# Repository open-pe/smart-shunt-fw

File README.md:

A versatile isolated power monitor based on INA228.
I made this for precision power metering and testing DCDC converters.

* Digital Signal isolators for i2c and alert
* Isolated power supply
* battery connector
* optional Vbus voltage divider for dc bus voltages above 85V
* programmable i2c address
* NTC for shunt temperature measurement (in addition to the INA228 internal temperature sensor)

# Building

## Platformio Setup

* [install script](https://docs.platformio.org/en/latest/core/installation/methods/installer-script.html)
* [setup shell commands](https://docs.platformio.org/en/latest/core/installation/shell-commands.html)
* [clion](https://docs.platformio.org/en/latest/integration/ide/clion.html)

select the board:

`pio run -e esp32s3`
or
`pio run -e stm32h5`

# TODO

- add ssa-100 plug?
- add ntc
- add pin header for chassis mount resistor
- jumper to disconnect on-board shunt?
- add RSN-50-50 footprint (no available)
- add external alert (for OC shutdown)
- add external IO pins?

Supported ADC:

* ADS1115 / ADS 1015 (for example with SSA-100)
* INA226 (16-bit)
* INA228 (20-bit, 85V)
* ADS1262 (32-bit)
* ADS131M0x (24-bit sim. sampling)
* TODO ADS127L11

On startup it detects the ADCs on the I2C bus using there default addresses.

I tested it on these MCUs:

* ESP8266
* ESP32
* ESP32-S3

The program reads voltage and current and computes power.
It integrates power for energy measurement using the trapezoidal rule.

# Output

* Serial (human friendly logs)
* UDP messages using InfluxDB line protocol

# Voltage Divider Resistors

Resistors with low temperature drift are favourable. Tolerance is not so important because we can simply calibrate.
Consider the ADC input impedance when designing the voltage divider.
Thin film or metal film resistors. Cheap ($.5) SMD chip resistors with 10ppm/°C.
Resistors with 5ppm/°C drift cost $2.
Choose resistors with equal drift, so drift get eliminated.

# Current Sense Resistors

https://www.researchgate.net/profile/Gunnar-Fernqvist/publication/224304168_Characteristics_of_burden_resistors_for_high-precision_DC_current_transducers/links/65ad0815f323f74ff1e064ab/Characteristics-of-burden-resistors-for-high-precision-DC-current-transducers.pdf
https://accelconf.web.cern.ch/p07/papers/MOPAN071.pdf
"The highest precision is offered by a proprietary Zeranin wire design from Hitec,"
=> Bulk Metal Foil or “foil”.

https://accelconf.web.cern.ch/p77/PDF/PAC1977_1810.PDF

10A <1ppm reference https://cds.cern.ch/record/643293/files/cer-002399330.pdf

https://www.datatec.eu/caenels-ct-100-c
https://www.datatec.eu/stromwandler-dcct
https://www.datatec.eu/caenels-ct-100v-p

A CT100-P with Y007810R0000B9L (10ohm, 0ppm/K) or 4-terminal Y169025R0000T9L (25ohm, 0.2ppm/K)
with 25ohms: 25mV/A (equiv burden 25mΩ, and almost no self-heat)

Low drift is important. Drift can be compensated with temperature measurement.
Consider max current and power dissipation. For resistances <=1mΩ it is hard to find low drift SMD chip resistors.
A chassis mount resistor might be a better choice for current measurement >40 A.

Riedon https://riedon.com/resistors/current-sense/
VPG

RUG-Z isabellenhuette

# Current Reference

https://doc.xdevs.com/doc/_Metrology/wang2014.pdf

# Resistor References

Tinsley 1682 https://www.ebay.com.au/itm/385633870779
J.L. William Scientific Instruments 0.1 Ohm Cal Standard DC Resistor (SN: 3127) (10 amp)
3928 (14amp)

## SMD Resistors

| MFR            | MPN                     | mΩ  | P   | Imax | tol | TCR           | padW/mm | padH/mm | 4wire | px100 |                                                                                       |
|----------------|-------------------------|-----|-----|------|-----|---------------|---------|---------|-------|-------|---------------------------------------------------------------------------------------|
| isabellenhütte | BVR-Z-R0003-1.0         | .3  | 11W |      | 1%  | 20ppm         | 5.5     | 1.6     | y     | $1.9  |                                                                                       |
| bourns         | CSS2H-2512R-L300F       | .3  | 6W  |      |     | 150ppm(50ppm) | 3.4     | 1.8     | n     | $     |                                                                                       |
| Milliohm (CN)  | HoLRS5930-0.3mR-1%      | .3  | 7W  |      | 1%  | 50ppm         | 7.6     | 4.2     | n     | $.24  |                                                                                       |
| vishay         | WSLP5931L3000FEA        | .3  | 10W |      | 1%  | 175ppm        | 7.75    | 5.2     | n     | $1.7  |                                                                                       |
| RESI (CN)      | SEWF3951DL300P9         | .3  | 15W |      | .5% | 25ppm         | 13      | 2       | n     | $2.2  |                                                                                       |
| isabellenhütte | BVR-Z-R0005-1.0         | .5  |     |      | 1%  | 20ppm         |         |         |       |       |                                                                                       |
|                | BVR-M-R0007-1.0         | .7  | 8W  |      | 1%  | 20ppm         |         |         |       |       |                                                                                       |
|                | BVR-M-R001              | 1   | 7W  |      |     | 50ppm         |         |         |       |       |                                                                                       |
| vishay         | Y14880R00100D0R         | 1   | 3W  |      | .5% | 15ppm         |         |         | y     |       |                                                                                       |
|                | WSK12161L000FEA/B       | 1   | 3W  |      | .1% | 20ppm         |         |         |       |       |                                                                                       |
|                | Y14880R00200B9R         | 2   | 3W  |      | .1% | 15ppm         |         |         | y     |       |                                                                                       |
|                | Y14730R00300B0R         | 3   | 3W  | 31A  | .1% | 5ppm          |         |         |       |       |                                                                                       |
|                | Y14750R10000B9R         | 100 |     |      | .1% | 10ppm         |         |         |       |       |                                                                                       |
| vpg            | PCS301                  |     |     | 15A  |     | 15ppm         |         |         |       |       | [pdf](https://vpgfoilresistors.com/products/current-sense-resistors/pcs301/datasheet) |
|                | SHR 4-2321 0R005 S 1% M | 5   | 40W |      |     | 5ppm          |         |         |       |       |                                                                                       |
|                | SHR 4-2321 0R005 S 1% L | 5   |     |      |     | 2ppm          |         |         |       |       |                                                                                       |
|                | PCS 301 0R100 S 1%      | 100 | 30W |      | 1%  | 3ppm          |         |         |       |       |                                                                                       |

[Digikey Chip Mount Resistors 40ppm 1mΩ ](https://www.digikey.de/short/8dbrqrp4)

TODO TCR curve
https://docs.rs-online.com/2d4e/0900766b81142cbf.pdf

Choose Chassis Mount resistor, suchs as the 1mOhm RSN-100-100B with 15ppm/k

## THT Resistors

Riedon PCS (10ppm, 40W)
PCS-0R001D1

| MPN                 | mΩ | tol | P   | Imax | TCR   | px  |
|---------------------|----|-----|-----|------|-------|-----|
| VPG Y07340R05000G9L | 50 | 2%  | 10W | 14A  | 2ppm  | $82 |
| Riedon PCS-0R001D1  | 1  |     | 40W | 200A | 10ppm | $40 |
| Riedon PCS-0R002D1  | 2  | .5% | 40W | 141A | 10ppm | $40 |
| Riedon PCS-0R005D1  | 5  | .5% | 40W | 89A  | 10ppm | $40 |
| PCS-0R01D1          | 10 |     | 40W | 63A  | 10ppm |     |
|                     |    |     |     |      |       |     |

Riedon USR 4- 3425 (3ppm, 30W, 0.01%)

## Chassis Mount Resistors

These commonly have lower tolerance and lower temp drift as compared to chip mount.
The larger surface of the resistive material and larger terminals decreases thermal resistance to ambient, which
reduces temperature rise.

|  |
|:-----------------------------------:|
|  Manganin (Riedon RSN, RSW and RS)  |

|                     | mΩ | P    | Tol   | TCR/K  | px    |
|---------------------|----|------|-------|--------|-------|
| Riedon RSW-50-50    | 1  |      | 0.25% | 15ppm  |       |
| Alpha FNPZR0040F    | 4  | 500w | 1%    | 1ppm   | $1060 |
| Alpha FNPZR0010B    | 1  | 500W | 0.1%  | 1ppm   | $1040 |
| FNPYR0020A          | 2  |      | 0.05% | 2.5ppm | $540  |
| Riedon RSN-100-100B | 1  | 10W  | 0.1%  | 15ppm  | $60   |
| RSA-50-100          | 1  | 5W   | 0.25% | 15ppm  | $30   |

## for battery monitoring

* SMD chip resistors are way cheaper (such as HoLRS5930-7W-0.25mR-1% )

|                                | mΩ | I(A) | tol |   |   | px |
|--------------------------------|----|------|-----|---|---|----|
| Milliohm HoFL2-75A-75mV-0.5%   | 1  | 75   | .5% |   |   | $5 |
| RESI ARCS8518JL100A9           | .1 |      | .5% |   |   |    |
| Milliohm HoFL3-8518-A-100uΩ-1% | .1 |      |     |   |   |    |
| HoFL2-200A-60mV-0.5%-HS        | .3 | 200  |     |   |   |    |

# 30A

ina228 has a shunt voltage range of 40.96 and 163.84 mV.
at a voltage drop of 40mV and 30A, we have 1.2 W of heat dissipation.

# applications

* bms/battery current sennsor
* smart shunt / lab shunt
* solar crowbar
* efuse
* mppt sensor

# set conversion time and averaging

* consder aliasing
* the ina22x ADC samples AND we sample the ina22x
* use conversion time to avoid aliasing during ADC
* use averaging to avoid aliasing during sampling the ina22x (i2c)
* when working with 50hz inverters, need a conversion time <=1ms.

# precision

* note that resistors change there resistance with temperature (see datasheet)
* use precision resistors
* keep temperature stable
* when measurement DCDC converter efficiency use 2x identical hardware. same chips and same resistors
* INA228 temp coefficient is 20ppm/°C, so choose resistor in that class
    * Ina228 features a temperature sensor

# AC Metrology

* Ti Design TIDU455A (MSP430AFE253, 24 Bit DeltaSigma ADC), class 0.2% accuracy
* Ti Eval Board EVM430-I2040S (MSP430I2040, 24bit, 8Khz or 80th harmonic of 50 Hz), <0.2% accuracy
    * AC, DC, 380V, 15 Amps
* Gossen Metrawatt Metrahit Energy (Starline Series) and
  Open-Source [IrDA USB](http://lemmini.de/IrDA%20USB/IrDA%20USB.html) (the Gossen USB X-Tra needs proprietary drivers,
  for windows only)
    * ESP32 has `UART_MODE_IRDA`, you only need the TFDU4101 [forum1](https://esp32.com/viewtopic.php?t=2766)

https://www.ti.com/lit/ug/tidua01/tidua01.pdf
https://www.analog.com/media/en/technical-documentation/data-sheets/ad637.pdf

* synchrounus subsampling (needs fast ADC)

* log-antilog

Thermal RMS Converters for ultimate

# EVM430

- the software "calibrator-20121120.exe" referenced in the datasheet is out-dated. I could not find a downlo
- use [MSP-EM-DESIGN-CENTER](https://www.ti.com/tool/MSP-EM-DESIGN-CENTER)
  , [intro](https://software-dl.ti.com/msp430/msp430_public_sw/mcu/msp430/EnergyMeasurementDesignCenter/1_40_00_03/release/EnergyMeasurementDesignCenter_1_40_00_03/docs/users_guide/html/Energy_Measurement_Technology_Guide_html/markdown/ch_designcenter.html)
  . works on Windows, Mac, Linux
- voltage sense (C14)  pin 1 and 2, A0.0+ and A0.0-
- Current Sense (C10) pin 3 and 4, A1.0+ and A1.0-
- there is a project "EVM430-i2040S_SH_1V_1C_50Hz"
- Double click the MCU and "Generate Code"
- Open generated src code project with CCSTUDIO
    - Could not get the online version to open the project (https://dev.ti.com/ide/)
    - the download IDE based on eclipse succeeded to build the generated project, but need MSP-FET programmer. not sure
      if an ordinary USB2UART addapter works?

# Isolated Current Sensor

DC-DC: MIE1W0505BGLVH-3R-Z (monolithic)
i2c: TPT72616-SO1R (3peak)

# Calibration

Console commands (serial, or over BLE as `cmd <line>`). Sampler names carry the board
prefix, if one is set (`ftr_DCCT`, not `DCCT`).

| Command | Effect |
|---|---|
| `calibrate <sampler> U\|I [*]<factor>` | gain factor, absolute or `*` relative (U is stored but not applied, `APPLY_U_GAIN_CAL=0`) |
| `calibrate <sampler> T <+/-degC>` | additive temperature offset for a TMP117 sampler, \|offset\| <= 2 °C |
| `calibrate <sampler> T clear` (or `T 0`) | remove the T offset; T is published uncorrected |
| `calibrate <sampler> T` | show the T offset |
| `calibrate` / `calibrate list` | every sampler's U/I factors and T offset |

The T offset is stored per sampler in its own NVS namespace (`tempoff`, key `s<storageId>`),
apart from the U/I EEPROM image. It applies only to TMP117 samplers, never to INA228 or ADS1262 die
temperatures. A missing, corrupt or out-of-range stored value loads as 0. The boot log prints
every applied offset. The TMP117's own TEMP_OFFSET register is left at its default.
See `src/temp_offset.h`.

Each offset is also published over BLE on every boot, every collector reconnect, every change,
and every 10 minutes. The collector writes it to the InfluxDB measurement
`smart_shunt_calibration` (`T_offset`, `status`, `event`), so you can undo the correction on stored
`T` later. An offset that could not be read is written as `status="invalid"` with no `T_offset`.
`doc/receiver.md` has the frame format.

Example: two TMP117s glued together at 19.5 °C, with 0x48 reading 0.145 °C above 0x49:

```
calibrate t17_48 T -0.145
```

Older U/I examples:

```

ina22x-resistor-range 0.000333333333333333 120
calibrate ESP32_INA228 U 1.00
calibrate ESP32_INA228 I 1.00

ina22x-resistor-range 0.0025 16
ina22x-resistor-range2 0.002 20  
ina22x-resistor-range3 0.002 20  

ina22x-resistor-range 0.001 40 
ina22x-resistor-range2 0.002 20 
ina22x-resistor-range3 0.002 20 

calibrate ESP32_INA228 U *1.000041
calibrate ESP32_INA228_2 U *1.000041
calibrate ESP32_INA228_3 U *1.0000233720530345

calibrate ESP32_INA228 I *1.0001119027192362
calibrate ESP32_INA228_2 I *0.9999067668612132

calibrate ESP32_INA228_3 I *1.0056727470362443

calibrate ESP32_INA228_2 U *1.00005
calibrate ESP32_INA228_3 I 1.0

calibrate ESP32_ADS1220 U *0.9985899493319389

calibrate ESP32_INA228 U *1.000032503295473
calibrate ESP32_INA228_2 U *1.000032503295473

calibrate ESP32_ADS1262 U 1.011406869687194   # an1->gnd
calibrate ESP32_ADS1262 U 1.0   # an1->gnd

calibrate ESP32_ADS1262 U 0.99882990

calibrate ESP32_ADS1262 U 1.01045

```

# Reference Designs

### LP-XDS110ET

[Design Files](https://www.ti.com/tool/LP-XDS110ET#design-files)

* ADC: ADS127L01IPBS
* Ref: REF6025IDGK (drift: 5ppm/K, noise: 5 µVRMS)
* Clock: SN74LVC2G74DCU
* Diff. Amp: THS4551IRUN
* Current Sense Amp: INA118UB

### ADS131B23

# Going Further

| error type      | mitigation                    | effort |
|-----------------|-------------------------------|--------|
| gain error      | single point calibration      | low    |
| gain temp drift | temperature measurement       | medium |
| non-linearity   | multi-point calibration (LUT) | medium |
| noise           | averaging                     | low    |

Simulatnous 2ch sampling instead of multiplexing.
Alternative: use 2 ADC chips

* ADS127L01 + THS4551 + INA169? ( see LP-XDS110ET circuit )

ADS131B23:

* 2x 24bit for redundant current measurement
* 1x 16bit for voltage measurement

# Selection Criteria

* Simultaneous sampling
    * more precise AC power sampling
    * easier to program
* PGA gain of >= 64
    * enable FSR of 40mV to directly measure voltage across current sense resistor without additional
      amplifier
* Linearity
    * Linearity can be improved with a look-up-table. Creating these tables require multi-point calibration.
    * Compare linearity error from the ADC data sheet to the temp drift of current sense resistor

# Voltage References

| MPN          | drift/K    | noise    | initial accuracy |                                                      |
|--------------|------------|----------|------------------|------------------------------------------------------|
| REF6025IDGK  | 5ppm       | 5 µVRMS  | ±0.05%           |                                                      |
| REF6225IDGKT | 3ppm       | 5 µVRMS  | ±0.05%           | [pdf](https://www.ti.com/lit/ds/symlink/ref6225.pdf) |
| LTC6655      | 2ppm       |          | ±0.025%          | for use with  LTC2508-32                             |
| LTC6652      | 5ppm       |          | 0.05%            |                                                      |
| LTZ1000      | 0.05ppm/°C | 1.2µVP-P |                  | for calibrators                                      |

https://youtu.be/upTgM_S5rAQ?si=JQq38q3_NsaYmSlv&t=2213

Fluke732A

https://github.com/marcoreps/ADRmu

Reference of all References
https://hackaday.com/2015/12/03/nuts-about-volts/
https://www.ptb.de/cms/service-seiten/news/forschungsnachricht.html?tx_news_pi1%5Bnews%5D=12912&tx_news_pi1%5Bcontroller%5D=News&tx_news_pi1%5Baction%5D=detail&tx_news_pi1%5Bday%5D=11&tx_news_pi1%5Bmonth%5D=10&tx_news_pi1%5Byear%5D=2023&cHash=8994d84faf7ba52fd97fa9559617df21

# Voltage Divider

VHD200 (digikey 15 weeks )
100mW. for measuring 80V at 2V ADC min 64k r_total

# Amps

THS4521 (ref6225)

# ADC Break-outs

https://protocentral.com/product/ads1115-16-bit-adc-4-channel-with-programmable-gain-amplifier/

https://protocentral.com/product/ads1220-24-bit-4-channel-low-noise-adc-breakout-board/

https://protocentral.com/product/protocentral-ads1262-32-bit-precision-adc-breakout-board/

https://www.mikroe.com/adc-15-click

https://www.waveshare.com/18983.htm (ADS1263)

MIKROE-4743 (ADS1262) 

# Misc

# Resolution and Noise

from https://www.ti.com/lit/ds/symlink/ads1231.pdf :
The RMS and Peak-to-Peak noise are referred to the input. The effective number of bits (ENOB) is defined as:
ENOB = ln (FSR/RMS noise)/ln(2)
Noise-Free Bits = ln (FSR/Peak-to-Peak Noise)/ln(2)
FSR (Full-Scale Range) = VREF/Gain.

https://electronics.stackexchange.com/questions/274606/whats-the-highest-precision-achieved-for-an-adc

Let's consider the application of measuring conversion efficency of a DC/DC converter.

According to the data sheet, INA228 measures power with total meusurement
error of 0.5% at full scale. We need two power monitors, one at the input and one at the output, total worst case error
of two devices is around 1%.

This error is too high, considering the DC/DC has an efficiency of > 95 %.
So let's have a look at more precise alternatives.

First

|                            |           |   |
|----------------------------|-----------|---|
| Gain Err (max)             | ±0.05 %   |   |
| Gain Temp Drift (max)      | 20 ppm/°C |   |
| ADC Resolution             | 20 bit    |   |
| Integral Non-Linearity     | 20 ppm    |   |
| Differential Non-Linearity | 0.2 LSB   |   |

For noise analysis, we need to define ADC measurement range and AC component frequency.
What is the ripple current, voltage and frequency?
Is the ripple periodic?
Is the ripple neglictable?
Can we smooth is out with a LP filter so we can assume DC only?
What digital filter does the ADC have?
Do we need an analog filter? Do we need to filter Aliasing?

TODO

* zero cross detection?
* AC metering?
* simulatnous filtering AC?

To work with some numbers, we define a working point:

- max current 40A
- current sense resistor 1mΩ
- max heat: 1.6 W (i2r)
- max voltage 40mV

* define a sampling rate
    * do we need to capture AC component or can we filter them?
    * if reactive power matters, we need simultanous ( https://www.ti.com/lit/an/slaa638a/slaa638a.pdf )

"The sample frequency is [...] 8 kHz that give us Nyquist
bandwidth of 4 kHz. This bandwidth is sufficient to cover the 66th harmonic for 60Hz AC, 80th harmonic for
50Hz AC frequency as wider bandwidth is usually needed for server power monitoring due to the nature of the
switching power supplies being monitored." -https://www.ti.com/lit/an/slaa638a/slaa638a.pdf

* :
* (max):
*

Note 7: Integral nonlinearity is defined as the deviation of a code from a
straight line passing through the actual endpoints of the transfer curve.
The deviation is measured from the center of the quantization band.

- https://www.ftcelectronics.sg/datasheets-58/LTC2508CDKD-32-TRPBF.pdf

# SPI Isolators

https://www.analog.com/media/en/technical-documentation/data-sheets/LTC6820.pdf
(needs 2 chips and 2 transformers)

https://www.mikroe.com/spi-isolator-5-click
using DCL541A01 (150Mbps, 3f/1r channels, default Low out)

https://www.electronics-lab.com/project/4-channel-spi-interface-isolator-with-three-forward-and-one-reverse-direction-channels/
based on ISO77418 (100Mbps, 5000V iso, 3f/1r ch, default High out)

# Tools

https://www.vishay.com/en/resistors/change-resistance-due-to-rtc-calculator/

# Heaters

https://www.amazon.de/Fyearfly-Temperatur-Heizplatte-Silikonkautschuk-elektrische/dp/B09MJ96BHK?_encoding=UTF8&pd_rd_i=B09MJ96BHK&pd_rd_w=NS24i&content-id=amzn1.sym.aab634e4-29b8-4848-9d24-fad213311357&pf_rd_p=aab634e4-29b8-4848-9d24-fad213311357&pf_rd_r=DECKKMJ91CMZ0HVX76A9&pd_rd_wg=tmowz&pd_rd_r=e27434a8-a59c-40f0-836b-ad5017ef97aa
https://www.digikey.de/en/products/detail/dfrobot/FIT0845/15848056
https://www.amazon.de/sourcing-map-selbstklebende-Heizelemente-Heizstreifen/dp/B0CTT8DCNG?mcid=2e62e8e0dd8637f59241dbf166a54a3d&th=1&psc=1&hvocijid=11518062653062946358-B0CTT8DCNG-&hvexpln=75&tag=googshopde-21&linkCode=df0&hvadid=696184104678&hvpos=&hvnetw=g&hvrand=11518062653062946358&hvpone=&hvptwo=&hvqmt=&hvdev=c&hvdvcmdl=&hvlocint=&hvlocphy=9043874&hvtargid=pla-2281435176898&psc=1&gad_source=1
https://electronics.stackexchange.com/questions/631263/using-mosfet-as-a-voltage-controlled-current-source

https://www.digikey.de/en/products/detail/innovative-sensor-technology-usa-division/HST-P11R0-1010-63A-2L-020/21407273

https://www.digikey.de/en/products/detail/riedon-products-by-bourns/PTCA-40/10271325

# Peltier

https://www.farnell.com/datasheets/4020641.pdf

# Heating Circuit

We want a precise temperature control loop to stabilize temperature of the resistive element.
The heater should be somehow coupled to the resistor for good heat transfer and it also needs
a heat-sink. We decide against PWM, since efficiency is not an issue, as we want to generate
heat anyway and it might cause unnecessary switching noise.

A linear control loop appear to make most sense. There are circuits like

the NTC is a LC471F3K, nominal 470 X at 25 °C, which acts as a sensor and heating element.

Despite the simplicity of this circuit, it not suitable in our application.
Measuring the temperature at the resistive element is important, since the resistor itself will produce heat.
Also finding an NTC with suitable power will likely be difficult.

We will measure

https://www.wellesu.com/10.1016/j.compag.2016.06.011
https://dr.lib.iastate.edu/server/api/core/bitstreams/d64d1b18-f1b3-41cd-be34-bc21360b506e/content
https://electronics.stackexchange.com/questions/690961/i-dont-understand-this-temperature-controller-circuits-behaviour
https://electronics.stackexchange.com/questions/498065/anemometer-with-opamp

https://www.circuitlab.com/circuit/63742k8e26j4/ntc-heater-control/

# Increasing Precision

The INA228 data sheet mentions a power monitoring accuracy of 0.5%. For monitoring DC/DC converters
with efficiencies of 95% or higher, INA228 accuracy is not sufficient. The integrated 0.5% precision oscillator adds
even more error for energy measurement.

# ADS1262 Journal

* ordered from protocentral
* are these genuine chips?
* review passive component circuitry of break-out board
* ads1262 needs at least 4.75V analog supply voltage !
* prefer MIKROE-4743 from digikey
* with PGA need at least 0.3V margin to rails (see Datasheet)
* linearity issue
    * sth appears to be wrong
    * absolute error seems quite high
    * maybe there is something wrong with the code?
* ads1220 appears to perform quite well
    * todo need spi isolator

# Measuring Single-Ended Signals with Diff-ADC

https://www.ti.com/lit/an/sbaa133a/sbaa133a.pdf?ts=1738999464967

THS4551

LTC2057 + LTC2508-32

# Current sense ampplifiers

MCP6C02

# Instrumentation AMps

- focus on precision (low noise, low offset, linearity)
- differential gain
- high CMRR
- high input impedance, low output impedance

https://www.ti.com/lit/ds/symlink/ina118.pdf?HQS=dis-dk-null-digikeymode-dsf-pf-null-wwe&ts=1739209355414&ref_url=https%253A%252F%252Fwww.ti.com%252Fgeneral%252Fdocs%252Fsuppproductinfo.tsp%253FdistId%253D10%2526gotoUrl%253Dhttps%253A%252F%252Fwww.ti.com%252Flit%252Fgpn%252Fina118#page=4&zoom=100,0,96
https://www.ti.com/solution/battery-cell-formation-test-equipment?variantid=34913&subsystemid=292016

|               |     | max gain    | noise                           | offset voltage (max) | offset drift (max) | gain drift ppm/K  G=1/G>1 | gain nonlinearity | common mode rej |                       |
|---------------|-----|-------------|---------------------------------|----------------------|--------------------|---------------------------|-------------------|-----------------|-----------------------|
| **INA190**    |     |             | 75 nV/√Hz                       | ±15 μV               | 0.08 uV/°C         | 7 ppm/°C                  | 100ppm            |                 |                       |
| INA848        |     | 2000 (fix)  | 1.5 nV/√Hz                      | 35µV                 | 0.45 μV/°C         | 5                         | 10ppm             | 132dB (min)     |                       |
| **INA851**    |     | 1000        | 3.2 nV/√Hz                      | 35 µV                | 0.3 µV/°C          | 5/35                      | 5ppm  (typ)       | 120db (min)     | with fully diff outp. |
| INA849        |     | 10000       | 1-nV/√Hz                        | 35 µV                | 0.4 μV/°C          | 5                         | 10ppm             |                 | for bat test          |
| INA826        |     |             | 18 nV/√Hz (G>=100)              | 150 µV               |                    | 1/35                      | 5ppm              |                 | bat test              |
| ina828        |     |             | 7 nV/√Hz                        | 50 µV                | 0.5 µV/°C          | 5/50                      | 15ppm             |                 |                       |
| INA2128       |     |             | 8 nV/√Hz at 1 kHz               | 50µV                 | 0.5 µV/°C          | ±10ppm                    |                   | 120db (min)     |                       |
| INA103        |     |             | 1nV/√Hz                         |                      |                    | ?                         | 100ppm            |                 |                       |
| **INA818**    |     |             | 8 nV/√Hz                        | 35µV                 |                    | 5/35                      | 15ppm (max)       |                 |                       |
| INA118        |     |             | 10nV/√Hz                        | 50µV                 | 0.5 µV/°C          |                           | 20ppm             |                 |                       |
| INA333        |     |             | 50 nV/√Hz                       | 25 μV                | 0.1 μV/°C          |                           | 10ppm             |                 |                       |
| AD624C        |     |             |                                 |                      |                    |                           |                   |                 |                       |
| LTC6915       | $9  | 4096 (prog) | 2.5µVP-P (0.01Hz to 10Hz)       | 10µV                 | 0.05µV/°C          |                           | 15ppm  (max)      |                 |                       |
| INA241A       | $3  |             | 28nV/Hz                         | 10µV                 |                    | 1ppm                      | 10ppm             |                 |                       |
| LTC1100       | $18 | 10 or 100   | ■ 0.1Hz to 10Hz Noise: 1.9µVP-P | 10uV (typ 1µV)       | 0.1µV/°C           | 4ppm                      | 8ppm (max)        |                 |                       |
| **LTC2053**   | $10 | 1000        | 2.5µVP-P (0.01Hz to 10Hz)       | 10µV                 | 0.05uV/°C          | 0                         | 3(typ) 12 (max)   | 116db (typ)     |                       |
| LT1167        |     |             | 0.1Hz to 10Hz Noise: 0.28μVP-P  | G = 10, 60μV Max     | 0.3μV/°C           | 50ppm       ?             | G = 10, 10ppm Max |                 |                       |
| LTC6363       |     |             | 0.2µVpp, DC to 10Hz (Typ)       |                      | 0.015μV/°C         |                           |                   | 150db (typ)     |                       |
| MCP6C02(G=20) |     |             | <=1Hz:0.48μVpp, 1.54            | G=20: 16µV           | 0.09 µV/°C         | 5ppm                      | 50ppm/100ppm      |                 | current sense amp     |

LNA10 (OPA4727) see https://www.youtube.com/watch?v=NoCp6cz32yo
Stanford Research SR560

https://www.thorlabs.com/thorproduct.cfm?partnumber=AMP100
https://github.com/marcoreps/low_noise_amplifier

LTC2057HV + LT1991A

# Op Amps

OPA4727
offset: 15µV (typ), 150µV (max)
drift: 0.3µV/°C (typ), 1.5µV/°C (max)
BANDWIDTH: 20MHz
LOW NOISE: 6nV/√Hz at 100kHz
AOL > 110dB

OPAx209
(higher drift, lower noise)
: 2.2 nV/√Hz at 1 kHz
Low Offset Voltage: 150 µV (Maximum)
drift: 3 µV/°C (max)

OPAx189
– Zero-drift: 0.005 μV/°C

- Ultra-low offset voltage: 3 μV maximum
  – CMRR: 168 dB
- en at 1 kHz: 5.2 nV/√Hz
- 0.1-Hz to 10-Hz noise: 0.1 µVPP

OPAx388

- offset voltage: ±0.25 µV
- drift ±0.005 µV/°C
- 140-dB CMRR
- Low noise: 7.0 nV√Hz at 1 kHz
- No 1/f noise: 0.14 uVPP (0.1 Hz to 10 Hz)
- https://www.ti.com/solution/analytical-lab-instrumentation#block-diagram
-

# Youtube

https://www.youtube.com/watch?v=upTgM_S5rAQ
https://www.youtube.com/watch?v=NoCp6cz32yo

# Literature

https://docs.ampnuts.ru/eevblog.docs/HP_Agilent_Keysight/HP%203458A%20Component-Level%20Information%20Packet.pdf
https://vtda.org/pubs/HP_Journal/HP_Journal_1989-04.pdf
https://doc.xdevs.com/doc/HP_Agilent_Keysight/3458A/ac_algo/Swerleins_Algorithm.pdf

* highest accuracy for lowest freq

# DataLogging

https://github.com/marcoreps/multiinstrumentalist

* HP3458A
* HP34420A
* W4950
* F8508A
* K2182A
* D1281

# Temp Sensors

TMP117 (i2c)

# ADC

important for dc metrology: stability and linearity (DC to 103- 104 Hz )
https://www.researchgate.net/publication/325285614_Analog-to-digital_conversion_beyond_20_bits_Applications_architectures_state_of_the_art_limitations_and_future_prospects

https://www.ti.com/lit/ug/tiduco9b/tiduco9b.pdf?ts=1739063348030&ref_url=https%253A%252F%252Fwww.google.com%252F

https://indico.cern.ch/event/814368/contributions/3397918/attachments/1832255/3000935/Class_0_ADC_-_Beev.pdf

https://www.welectron.com/Digilent-MCC-172-IEPE-Sensor-DAQ-HAT-for-Raspberry-Pi-2-CH-24-bit

# Thermal EMF

https://www.ab-precision.de/products/cables-accessories/

https://www.ni.com/docs/de-DE/bundle/ni-switch/page/thermal-emf-and-offset-voltage.html

https://www.youtube.com/watch?v=EW58sm8ciWk

https://www.youtube.com/watch?v=KiYhEP6m7Pc

https://dam-assets.fluke.com/s3fs-public/p18-21.pdf

https://www.eevblog.com/forum/metrology/binding-postsbanana-sockets-cleaning-on-dmmsmetrology-lab-gear/

https://www.eevblog.com/forum/chat/help-wanted-low-and-high-ohm-measuremet/?action=dlattach;attach=35289

Pomona 2305

diy Fluke 5440A-7003
https://www.eevblog.com/forum/metrology/diy-low-emf-cable-and-connectors/msg545213/#msg545213

Riedon RSN Brass Terminals:
Thermal EMF to copper wire ~2µV, at 50mV FSR this is 40ppm.

# Gold Plated Banana Plugs

CT3099

[Pomona 4897-2](https://www.digikey.de/en/products/detail/pomona-electronics/4897-2/737024)

https://mm.digikey.com/Volume0/opasdata/d220001/medias/docus/4846/DS_1768_Catalog.pdf

Multicomp 1699021

Farnell has more than digikey

# Kelvin Clips Gold Plated

CTM-78K
CTM-75K

# Linearity, INL

https://xdevs.com/article/inlperf/

# CERN HPM7177 (open soruce) DMM

https://ohwr.org/project/opt-adc-10k-32b-1cha/-/wikis/home
base on AD7177-2
effective resolution >23 bits for BW < 10 Hz
temperature drift (offset and gain) <0.1 ppm/°C from 20°C to 40°C
INL <0.6 ppm (0 to +10 V)

# Notes on Precision

High-Precision (ppm range) current sensing can be tricky due to thermal effects.
Most resistors have a positive temperature coefficient when they heat up, so current is measured too high.
A closed-loop temperature control of the current sense resistor can improve stability.
There are Vishay VPG resistors with 0ppm/K or <1ppm/K, but only in the sub-1W range, so not suitable for higher
currents.
Low burden voltage decreases resistor heating but Thermoelectric noise (thermal EMF) becomes more dominant.
Use as few material boundaries, not connectors, no gold, just copper. Use un-finished copper trace to contact resistors
with screw terminals, which are usually some sort of brass.

Offset drifts can be compensated with a chopper circuit, that frequently bypasses the load current and measures the
offset current
which is then compensated in following measurement.

If you want to measure ratio of currents, use the same sense resistors and chop both currents over it to eliminate
drift.
This way any error produced by the resistor is eliminated, offset by thermal EMF is still relevant and the ADC
performance
(offset and linearity).

For best linearity, highest thermal imunity and lowest drift, consider using DC-current transformers (DCCT).

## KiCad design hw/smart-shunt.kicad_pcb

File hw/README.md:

This is a energy monitor based on the INA228.
It comes with a Würth PowerPlus M5 terminals and a 4026 shunt resistor slot for resistors from e.g.
Bourns, Vishay, Isabellenhütte.
Alternately you can use chassis mount resistors such as the Riedon RSN series with very low temperature drift.

The board comes with an isolated dc-dc and i2c isolator (and another isolator for the alert signal).

## Measuring voltage >85V

Although the INA228 only supports Vbus up to 85V you can measure much higher voltages (I tested up to 400V DC).
Put the shunt on the ground sound and populate the voltage divider with THT precision resistors or SMD chip resistors.

For high voltages higher than 85V the `IN-` pin must be pulled to ground. There will be a lot of noise otherwise.

# isolators

TPT774x:

TPT7721-SO1R:
2 ch

FXMAR2102UMX:
2ch bidirectional! $.32

INA241

* motor drives
  https://www.ti.com/de-de/video/6314459715112

INA296A

* Version A: ±0.01%, ±1ppm/°C drift
* app: Test & Meausrement
* https://github.com/CrabLabsLLC/OpenMD/blob/develop/docs/Schematic.pdf
*

TPA6271:
110V 16bit power monitor

|                | Vbus   | CMRR(min) | BW      | OffsetErr | Gain Err(max) | NonLinErr | TempDrift  | BiDir? | ShuntVRange | Outp       |                                                                  |
|----------------|--------|-----------|---------|-----------|---------------|-----------|------------|--------|-------------|------------|------------------------------------------------------------------|
| 3peak TPA6271  | 102.4V | 120 dB    | 140µs   | ±10µV     | 0.15%         |           | 10ppm/C    | y      | 81.92mV     | i2c, 16bit | [pdf](https://static.3peak.com/res/doc/ds/Datasheet_TPA6271.pdf) |
| TI INA226      |        |           |         |           |               |           |            |        |             |            |                                                                  |
| TI INA228      |        | 154 dB    |         |           | ±0.05%        | ±0.002%   | ±20 ppm/C  | y      |             |            |                                                                  |
| TI INA229      |        |           |         |           |               |           |            |        |             |            |                                                                  |
| TI INA241      |        |           |         |           |               |           |            |        |             |            | enhanced PWM-suppr.                                              |
| TI **INA296A** | 110V   | 150 dB    | 1.1MHz  | ±10µV     | ±0.01%        | ±0.001%   | ±1ppm/°C   | y      |             |            |                                                                  |
| TI INA310A     | 110V   | 140 dB    | 1.3 MHz | ±20 µV    | ±0.15%        | ±0.01%    | 10ppm/C    |        |             |            |                                                                  |
| LMV93x-N       | n/a    | 60 dB     | 1.4 MHz | 4 mV      |               |           |            |        |             |            |                                                                  |
| THS4551        |        |           | 150 MHz | ±175 µV   |               |           |            |        |             |            |                                                                  |
| AMC1300        |        |           |         |           | ±0.3%         | 0.03%     | ±30 ppm/°C |        |             |            | isolated amp                                                     |

We can calibrate Gain Err/ Gain Offset with 2 point calibration.
Non-linearity can be reduced by multi-point calibration (LUT).
TempDrift can be compensated with a temperature sensor and the drift curve from the datasheet.

Non linearity and temp drift are crucial since harder to compensate.

ADC

| MPN        | eff resolution | gain   | sps | ch | tempDrift | NonLinear | offset  | OffsetDrift | GainErr | GainDrift |
|------------|----------------|--------|-----|----|-----------|-----------|---------|-------------|---------|-----------|
| ADS1220    | 20bit          | 1..128 | 2k  | 4  | 5 ppm/C   |           |         |             |         |           |
| ADS127L21B |                |        |     |    |           | 0.5ppm    | +-250µV | 200 nV/C    |         | 1ppm/C    |
| ADS127L11  |                |        |     |    |           |           |         |             |         |           |
| ADS124S06  |                |        |     |    |           |           |         |             |         |           |

## Analog Version

- INA296A + ADS1220 (or ADS127L21B)
- SPI need 3 up, and 2 down ch. (or only 1 down?)
- analog level translation for oscilloscope connection. using high-side current sense circuit?
   ( LMV93x-N datasheet)
    - unfortunately the INA296 does not give access to (-) inp of

- THS4551 (amp) +

https://www.ti.com/solution/power-analyzer?variantid=34826&subsystemid=23445

PwrTool 500

# Thermal
20A with Y14880R00200B9R 2mΩ temp-rise 18 => 38°C  ∆20°C (ina229 package: 25°C)

# 24bit
REF6225IDGKT
ads127 (
ADS131M02 (apps: power, battery) https://www.ti.com/lit/ds/symlink/ads131m02.pdf

# 32bit
ADS1288

SPI:
CS (->)
SCLK ->
MOSI ->
MISO <-
DRDY <-

ISO6721BDR, 3kv, 50mbps, 2/0ch
ISO6731DWR, 5kv, 50mbps, 2/1ch

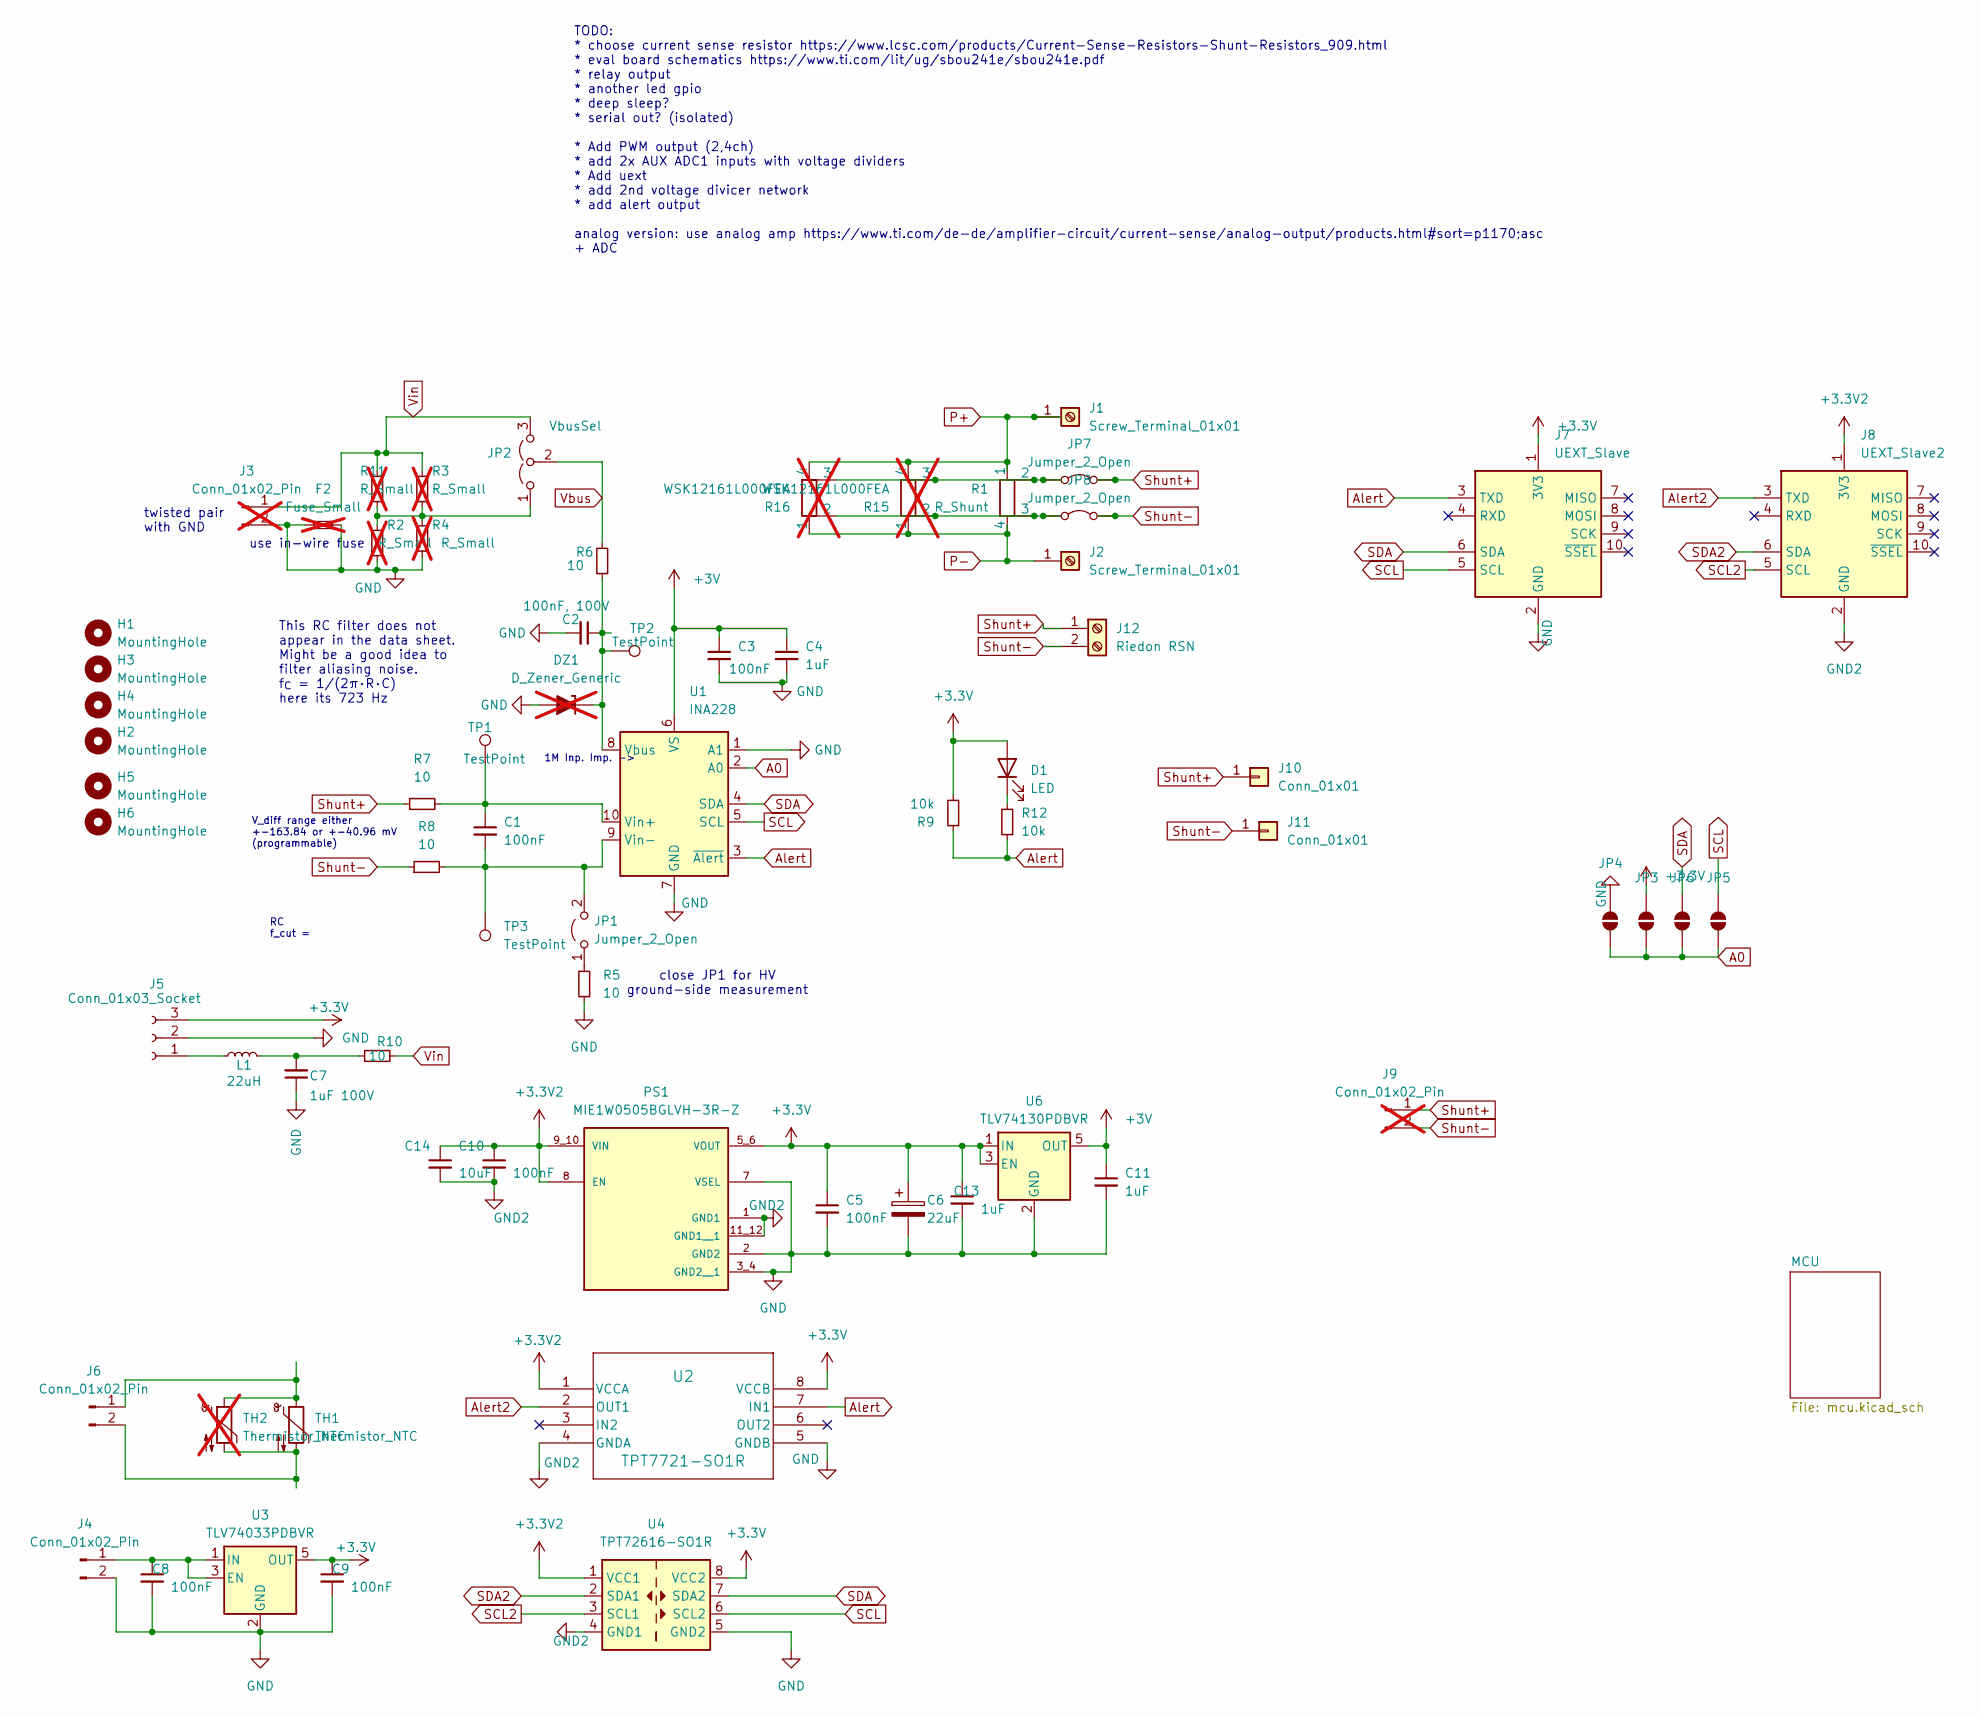
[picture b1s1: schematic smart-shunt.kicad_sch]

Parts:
C1, C3, C5, C8, C9, C10: 100nF; C_0805_2012Metric
C2: 100nF, 100V; C_0805_2012Metric
C4, C11, C13: 1uF; C_0805_2012Metric
C6: 22uF; CP_Elec_6.3x5.9; MPN A766EB226M1DLAE060
C7: 1uF 100V; C_0805_2012Metric
C14: 10uF; C_0805_2012Metric
D1: LED; LED_0805_2012Metric
DZ1: D_Zener_Generic; not fitted
F2: Fuse_Small; Fuseholder_Clip-5x20mm_Littelfuse_100_Inline_P20.50x4.60mm_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; not fitted
H1, H2, H3, H4, H5, H6: MountingHole; MountingHole_2.2mm_M2
J1, J2: Screw_Terminal_01x01; Wuerth_PowerPlus_M5_Nut
J3, J9: Conn_01x02_Pin; PinHeader_1x02_P2.54mm_Vertical; not fitted
J4, J6: Conn_01x02_Pin; PinHeader_1x02_P2.54mm_Vertical
J5: Conn_01x03_Socket; PinHeader_1x03_P2.54mm_Vertical
J7: UEXT_Slave; PinHeader_2x05_P2.54mm_Vertical
J8: UEXT_Slave2; PinHeader_2x05_P2.54mm_Vertical
J10, J11: Conn_01x01; PinHeader_1x01_P2.54mm_Vertical
J12: Riedon RSN; RiedonRSN
JP1: Jumper_2_Open; SolderJumper-2_P1.3mm_Open_RoundedPad1.0x1.5mm
JP2: VbusSel; SolderJumper-3_P1.3mm_Open_RoundedPad1.0x1.5mm
JP3, JP4, JP5, JP6: SolderJumper_2_Open; SolderJumper_0402_1005Metric
JP7, JP8: Jumper_2_Open; SolderJumper_0402_1005Metric_Bridged
L1: 22uH; L_0805_2012Metric; MPN MLZ2012N220LT000
PS1: MIE1W0505BGLVH-3R-Z; CONV_MIE1W0505BGLVH-3R-Z; PARTREV 0.8
R1: R_Shunt; R_Shunt_Isabellenhuette_BVR4026
R2, R11: R_Small; R_Axial_DIN0204_L3.6mm_D1.6mm_P7.62mm_Horizontal; not fitted
R3, R4: R_Small; R_0805_2012Metric; not fitted
R5, R6, R10: 10; R_0805_2012Metric
R7, R8: 10; R_0805_2012Metric_Bridged
R9, R12: 10k; R_0805_2012Metric
R15: WSK12161L000FEA; SMT_61L000FEA_VIS; not fitted
R16: WSK12161L000FEA; CSM3637_1-2mOHM_VIS; not fitted
TH1: Thermistor_NTC; R_0402_1005Metric
TH2: Thermistor_NTC; R_0402_1005Metric; not fitted
TP1, TP2, TP3: TestPoint; TestPoint_Pad_D1.0mm
U1: INA228; VSSOP-10_3x3mm_P0.5mm
U2: TPT7721-SO1R; SOP-8_3.9x4.9mm_P1.27mm
U3: TLV74033PDBVR; SOT-23-5
U4: TPT72616-SO1R; SOIC-8_3.9x4.9mm_P1.27mm
U6: TLV74130PDBVR; SOT-23-5

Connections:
+3.3V: C5.1, C6.1, C9.1, C13.1, D1.2 (A), J5.3, J7.1 (3V3), JP3.2 (B), PS1.5_6 (VOUT), R9.2, U2.8 (VCCB), U3.5 (OUT), U4.8 (VCC2), U6.1 (IN), U6.3 (EN); also elsewhere on the board
+3.3V2: C10.1, C14.1, J8.1 (3V3), PS1.8 (EN), PS1.9_10 (VIN), U2.1 (VCCA), U4.1 (VCC1)
+3V: C3.1, C4.1, C11.1, U1.6 (VS), U6.5 (OUT)
A0: JP3.1 (A), JP4.1 (A), JP5.1 (A), JP6.1 (A), U1.2 (A0)
Alert: J7.3 (TXD), R9.1, R12.2, U1.3 (~Alert), U2.7 (IN1)
Alert2: J8.3 (TXD), U2.2 (OUT1)
GND: C2.2, C3.2, C4.2, C5.2, C6.2, C7.1, C8.2, C9.2, C11.2, C13.2, DZ1.2 (A), F2.1, F2.2, J3.2, J4.2, J5.2, J7.2 (GND), JP4.2 (B), PS1.2 (GND2), PS1.3_4 (GND2__1), PS1.7 (VSEL), R2.1, R4.1, R5.1, U1.1 (A1), U1.7 (GND), U2.5 (GNDB), U3.2 (GND), U4.5 (GND2), U6.2 (GND)
GND2: C10.2, C14.2, J8.2 (GND), PS1.1 (GND1), PS1.11_12 (GND1__1), U2.4 (GNDA), U4.4 (GND1)
unnamed: C7.2, L1.2, R10.1
unnamed: D1.1 (K), R12.1
unnamed: C8.1, J4.1, U3.1 (IN), U3.3 (EN)
unnamed: J5.1, L1.1
unnamed: J6.1, TH1.1, TH2.1
unnamed: J6.2, TH1.2, TH2.2
unnamed: JP1.1 (A), R5.2
unnamed: C1.2, JP1.2 (B), R8.2, TP3.1, U1.9 (Vin-)
unnamed: JP2.1 (A), R2.2, R3.1, R4.2, R11.1
unnamed: JP7.1 (A), R1.2, R15.3, R16.3
unnamed: JP8.1 (A), R1.3, R15.2, R16.2
unnamed: C2.1, DZ1.1 (K), R6.1, TP2.1, U1.8 (Vbus)
unnamed: C1.1, R7.2, TP1.1, U1.10 (Vin+)
P+: J1.1, R1.1, R15.4, R16.4
P-: J2.1, R1.4, R15.1, R16.1
SCL: J7.5 (SCL), JP5.2 (B), U1.5 (SCL), U4.6 (SCL2); also elsewhere on the board
SCL2: J8.5 (SCL), U4.3 (SCL1)
SDA: J7.6 (SDA), JP6.2 (B), U1.4 (SDA), U4.7 (SDA2); also elsewhere on the board
SDA2: J8.6 (SDA), U4.2 (SDA1)
Shunt+: J9.1, J10.1, J12.1, JP7.2 (B), R7.1
Shunt-: J9.2, J11.1, J12.2, JP8.2 (B), R8.1
Vbus: JP2.2 (C), R6.2
Vin: J3.1, JP2.3 (B), R3.2, R10.2, R11.2

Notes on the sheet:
1M Inp. Imp. ->
RC f_cut =
This RC filter does not appear in the data sheet. Might be a good idea to filter aliasing noise. f_{C} = 1/(2π·R·C) here its 723 Hz
close JP1 for HV ground-side measurement
use in-wire fuse
TODO: * choose current sense resistor https://www.lcsc.com/products/Current-Sense-Resistors-Shunt-Resistors_909.html * eval board schematics https://www.ti.com/lit/ug/sbou241e/sbou241e.pdf * relay output * another led gpio * deep sleep? * serial out? (isolated) * Add PWM output (2,4ch) * add 2x AUX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
V_diff range either +-163.84 or +-40.96 mV (programmable)
twisted pair with GND

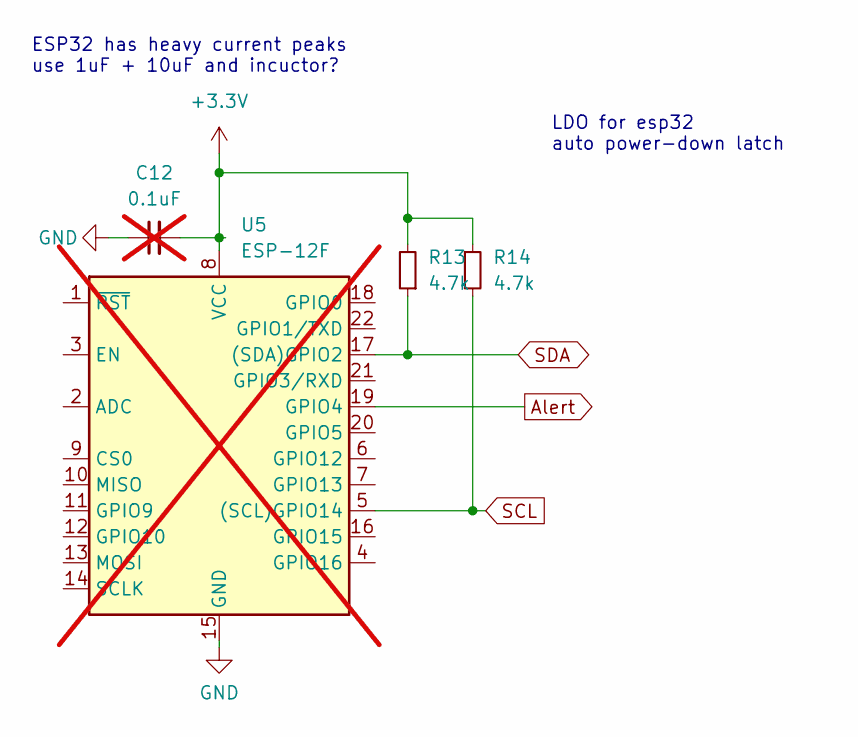
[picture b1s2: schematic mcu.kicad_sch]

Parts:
C12: 0.1uF; C_0805_2012Metric; not fitted
R13, R14: 4.7k; R_0805_2012Metric
U5: ESP-12F; ESP-12E; not fitted

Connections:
+3.3V: C12.2, R13.2, R14.1, U5.8 (VCC); also elsewhere on the board
unnamed: C12.1, U5.15 (GND)
SCL: R14.2, U5.5 ((SCL)GPIO14); also elsewhere on the board
SDA: R13.1, U5.17 ((SDA)GPIO2); also elsewhere on the board

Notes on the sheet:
ESP32 has heavy current peaks use 1uF + 10uF and incuctor?
LDO for esp32 auto power-down latch

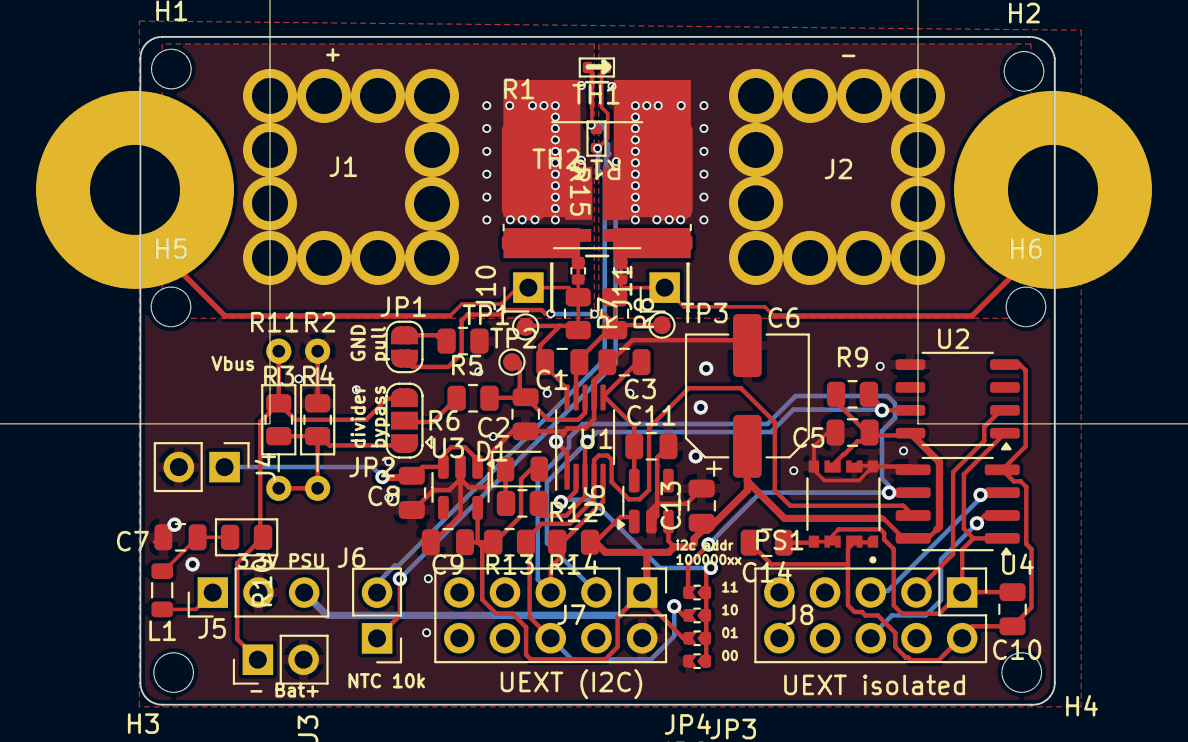
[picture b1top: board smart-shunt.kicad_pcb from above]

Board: 2 copper layers, 50.8 x 37.1 mm, 66 parts (1 on the bottom side), 31 nets.

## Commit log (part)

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2023-03-08 init
2023-03-08 writing influxdb
2023-03-09 interrupt based (but unstable)
2023-03-09 use sampleBuf
2023-03-09 working at 507 sps (no influx)
2023-03-09 fix influxdb flush interval
2023-03-10 working (no influx)
2023-03-11 influx udp write
2023-03-12 add printTime
2023-03-12 move ADC reading to main loop
2023-03-23 update 500ms
2023-03-23 esp adc
2023-03-23 new sampling code wip
2023-03-23 sampling wip
2023-03-24 snap
2023-03-27 platform.io
2023-03-27 platformio compiling
2023-03-27 running on esp32-s3
2023-03-27 batched point write
2023-03-27 work
2023-03-27 reset delay
2023-03-28 Auto stash before merge of "main" and "origin/main"
2023-03-30 esp32 adc dma
2023-03-30 workspace
2023-05-03 ina226
2023-05-04 ads move interrupt setup to init()
2023-05-04 ina226 calib
2023-05-28 add ina228
2023-05-28 add storage and display
2023-05-30 tele add dt_max, timeouts
2023-05-30 udpFlushString
2024-12-09 changes from backup
2024-12-09 add kicad project
2024-12-19 add real-time loop, read UART inp until eol
2024-12-19 ina228 fix shunt cal
2024-12-19 finished pcb
2024-12-20 add battery connector and LDO
2024-12-24 hw: 2nd LDO, mounting holes
2024-12-24 docs
2024-12-24 ide stuff
2024-12-26 readme
2025-01-24 add support for 2nd ina228
2025-01-27 add 3rd ina228 & ads1220
2025-02-11 python scripts
2025-02-11 usb console
2025-02-11 add temperature reading
2025-02-11 calibration gains storage
2025-02-11 add ads1262
2025-02-11 etc adc
2025-09-27 ac rejection
2025-09-27 add riedon rsn footprint, copper only path
2025-10-20 ads131 somewhat working
2025-10-20 ads131 working
2025-10-28 move images
2025-10-28 python dmm
2025-10-28 add TMP117
2025-10-28 influxdb num precision
2025-10-28 fix include
2025-10-28 ina228 dc avg
2025-10-28 ina228 recover timeout
2025-11-02 move files
2025-11-02 add ble srv
2025-11-02 imporved influxdb buffer
2025-11-02 pins
2025-11-02 disable LCD, ble server
2025-11-02 ina228 select channels
2025-11-02 log level info
2025-11-02 tmp117 fixes
2025-11-02 add partitions file
2025-11-07 ina228: check shorted pins
2025-11-07 ble only
2025-12-17 nimble
2025-12-17 add dummy
